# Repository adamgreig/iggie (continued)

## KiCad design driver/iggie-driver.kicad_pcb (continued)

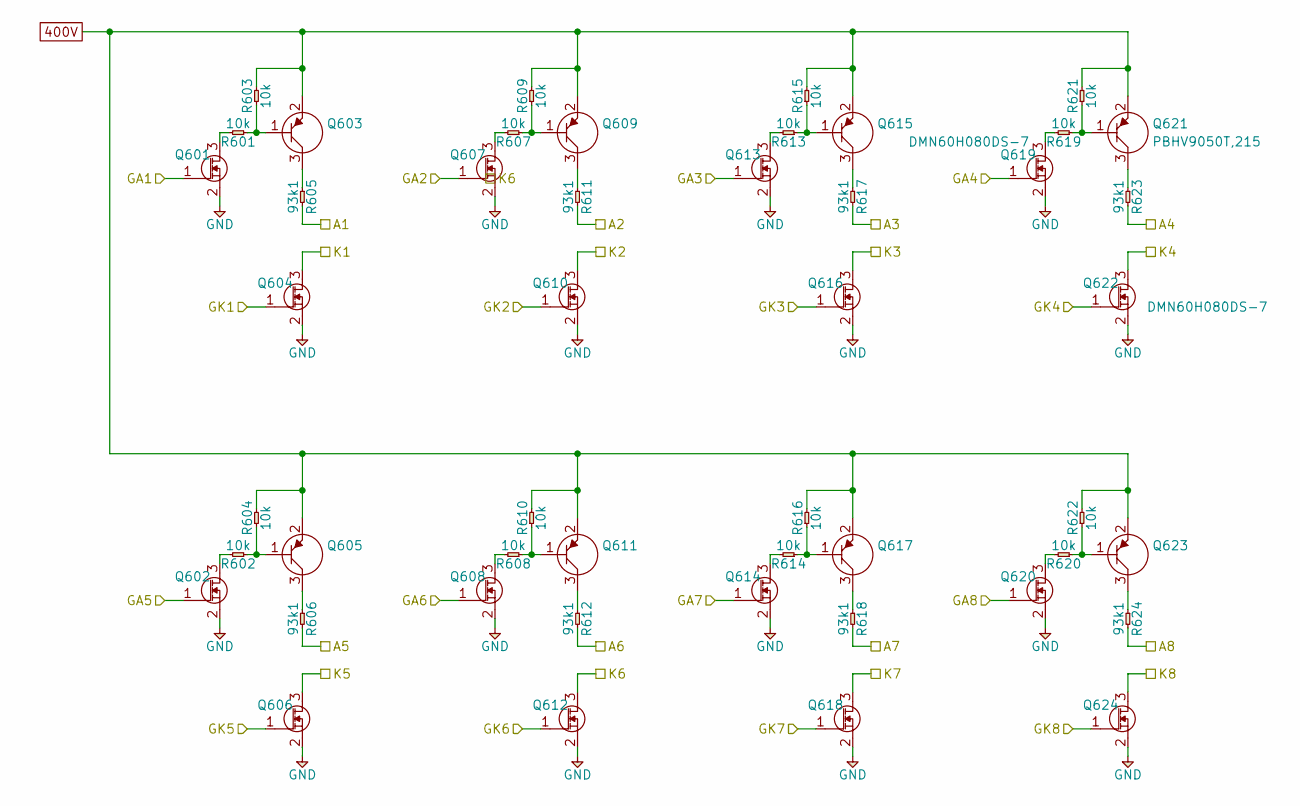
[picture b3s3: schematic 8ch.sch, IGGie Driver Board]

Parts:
Q301, Q302, Q304, Q306, Q307, Q308, Q310, Q312, Q313, Q314, Q316, Q318, Q319, Q320, Q322, Q324: DMN60H080DS-7; SOT-23; Farnell 3127344
Q303, Q305, Q309, Q311, Q315, Q317, Q321, Q323: PBHV9050T,215; SOT-23; Farnell 1829318
R301, R302, R303, R304, R307, R308, R309, R310, R313, R314, R315, R316, R319, R320, R321, R322: 10k; 1206; Voltage 500V; Farnell 1750850
R305, R306, R311, R312, R317, R318, R323, R324: 93k1; 1206; Voltage 500V; Farnell 2327389

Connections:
400V: Q303.2 (E), Q305.2 (E), Q309.2 (E), Q311.2 (E), Q315.2 (E), Q317.2 (E), Q321.2 (E), Q323.2 (E), R303.2, R304.2, R309.2, R310.2, R315.2, R316.2, R321.2, R322.2; also elsewhere on the board
/Channels/A1: R305.2; also elsewhere on the board
/Channels/A2: R311.2; also elsewhere on the board
/Channels/A3: R317.2; also elsewhere on the board
/Channels/A4: R323.2; also elsewhere on the board
/Channels/A5: R306.2; also elsewhere on the board
/Channels/A6: R312.2; also elsewhere on the board
/Channels/A7: R318.2; also elsewhere on the board
/Channels/A8: R324.2; also elsewhere on the board
/Channels/GA1: Q301.1 (G); also elsewhere on the board
/Channels/GA2: Q307.1 (G); also elsewhere on the board
/Channels/GA3: Q313.1 (G); also elsewhere on the board
/Channels/GA4: Q319.1 (G); also elsewhere on the board
/Channels/GA5: Q302.1 (G); also elsewhere on the board
/Channels/GA6: Q308.1 (G); also elsewhere on the board
/Channels/GA7: Q314.1 (G); also elsewhere on the board
/Channels/GA8: Q320.1 (G); also elsewhere on the board
/Channels/GK1: Q304.1 (G); also elsewhere on the board
/Channels/GK2: Q310.1 (G); also elsewhere on the board
/Channels/GK3: Q316.1 (G); also elsewhere on the board
/Channels/GK4: Q322.1 (G); also elsewhere on the board
/Channels/GK5: Q306.1 (G); also elsewhere on the board
/Channels/GK6: Q312.1 (G); also elsewhere on the board
/Channels/GK7: Q318.1 (G); also elsewhere on the board
/Channels/GK8: Q324.1 (G); also elsewhere on the board
/Channels/K1: Q304.3 (D); also elsewhere on the board
/Channels/K2: Q310.3 (D); also elsewhere on the board
/Channels/K3: Q316.3 (D); also elsewhere on the board
/Channels/K4: Q322.3 (D); also elsewhere on the board
/Channels/K5: Q306.3 (D); also elsewhere on the board
/Channels/K6: Q312.3 (D); also elsewhere on the board
/Channels/K7: Q318.3 (D); also elsewhere on the board
/Channels/K8: Q324.3 (D); also elsewhere on the board
GND: Q301.2 (S), Q302.2 (S), Q304.2 (S), Q306.2 (S), Q307.2 (S), Q308.2 (S), Q310.2 (S), Q312.2 (S), Q313.2 (S), Q314.2 (S), Q316.2 (S), Q318.2 (S), Q319.2 (S), Q320.2 (S), Q322.2 (S), Q324.2 (S); also elsewhere on the board
unnamed: Q301.3 (D), R301.2
unnamed: Q302.3 (D), R302.2
unnamed: Q303.1 (B), R301.1, R303.1
unnamed: Q303.3 (C), R305.1
unnamed: Q305.1 (B), R302.1, R304.1
unnamed: Q305.3 (C), R306.1
unnamed: Q307.3 (D), R307.2
unnamed: Q308.3 (D), R308.2
unnamed: Q309.1 (B), R307.1, R309.1
unnamed: Q309.3 (C), R311.1
unnamed: Q311.1 (B), R308.1, R310.1
unnamed: Q311.3 (C), R312.1
unnamed: Q313.3 (D), R313.2
unnamed: Q314.3 (D), R314.2
unnamed: Q315.1 (B), R313.1, R315.1
unnamed: Q315.3 (C), R317.1
unnamed: Q317.1 (B), R314.1, R316.1
unnamed: Q317.3 (C), R318.1
unnamed: Q319.3 (D), R319.2
unnamed: Q320.3 (D), R320.2
unnamed: Q321.1 (B), R319.1, R321.1
unnamed: Q321.3 (C), R323.1
unnamed: Q323.1 (B), R320.1, R322.1
unnamed: Q323.3 (C), R324.1

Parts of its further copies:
Q401, Q402, Q404, Q406, Q407, Q408, Q410, Q412, Q413, Q414, Q416, Q418, Q419, Q420, Q422, Q424, Q501, Q502, Q504, Q506, Q507, Q508, Q510, Q512, Q513, Q514, Q516, Q518, Q519, Q520, Q522, Q524, Q601, Q602, Q604, Q606, Q607, Q608, Q610, Q612, Q613, Q614, Q616, Q618, Q619, Q620, Q622, Q624: DMN60H080DS-7; SOT-23; Farnell 3127344
Q403, Q405, Q409, Q411, Q415, Q417, Q421, Q423, Q503, Q505, Q509, Q511, Q515, Q517, Q521, Q523, Q603, Q605, Q609, Q611, Q615, Q617, Q621, Q623: PBHV9050T,215; SOT-23; Farnell 1829318
R401, R402, R403, R404, R407, R408, R409, R410, R413, R414, R415, R416, R419, R420, R421, R422, R501, R502, R503, R504, R507, R508, R509, R510, R513, R514, R515, R516, R519, R520, R521, R522, R601, R602, R603, R604, R607, R608, R609, R610, R613, R614, R615, R616, R619, R620, R621, R622: 10k; 1206; Voltage 500V; Farnell 1750850
R405, R406, R411, R412, R417, R418, R423, R424, R505, R506, R511, R512, R517, R518, R523, R524, R605, R606, R611, R612, R617, R618, R623, R624: 93k1; 1206; Voltage 500V; Farnell 2327389

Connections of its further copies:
400V: Q403.2 (E), Q405.2 (E), Q409.2 (E), Q411.2 (E), Q415.2 (E), Q417.2 (E), Q421.2 (E), Q423.2 (E), Q503.2 (E), Q505.2 (E), Q509.2 (E), Q511.2 (E), Q515.2 (E), Q517.2 (E), Q521.2 (E), Q523.2 (E), Q603.2 (E), Q605.2 (E), Q609.2 (E), Q611.2 (E), Q615.2 (E), Q617.2 (E), Q621.2 (E), Q623.2 (E), R403.2, R404.2, R409.2, R410.2, R415.2, R416.2, R421.2, R422.2, R503.2, R504.2, R509.2, R510.2, R515.2, R516.2, R521.2, R522.2, R603.2, R604.2, R609.2, R610.2, R615.2, R616.2, R621.2, R622.2; also elsewhere on the board
/Channels/A9: R405.2; also elsewhere on the board
/Channels/A10: R411.2; also elsewhere on the board
/Channels/A11: R417.2; also elsewhere on the board
/Channels/A12: R423.2; also elsewhere on the board
/Channels/A13: R406.2; also elsewhere on the board
/Channels/A14: R412.2; also elsewhere on the board
/Channels/A15: R418.2; also elsewhere on the board
/Channels/A16: R424.2; also elsewhere on the board
/Channels/A17: R505.2; also elsewhere on the board
/Channels/A18: R511.2; also elsewhere on the board
/Channels/A19: R517.2; also elsewhere on the board
/Channels/A20: R523.2; also elsewhere on the board
/Channels/A21: R506.2; also elsewhere on the board
/Channels/A22: R512.2; also elsewhere on the board
/Channels/A23: R518.2; also elsewhere on the board
/Channels/A24: R524.2; also elsewhere on the board
/Channels/A25: R605.2; also elsewhere on the board
/Channels/A26: R611.2; also elsewhere on the board
/Channels/A27: R617.2; also elsewhere on the board
/Channels/A28: R623.2; also elsewhere on the board
/Channels/A29: R606.2; also elsewhere on the board
/Channels/A30: R612.2; also elsewhere on the board
/Channels/A31: R618.2; also elsewhere on the board
/Channels/A32: R624.2; also elsewhere on the board
/Channels/GA9: Q401.1 (G); also elsewhere on the board
/Channels/GA10: Q407.1 (G); also elsewhere on the board
/Channels/GA11: Q413.1 (G); also elsewhere on the board
/Channels/GA12: Q419.1 (G); also elsewhere on the board
/Channels/GA13: Q402.1 (G); also elsewhere on the board
/Channels/GA14: Q408.1 (G); also elsewhere on the board
/Channels/GA15: Q414.1 (G); also elsewhere on the board
/Channels/GA16: Q420.1 (G); also elsewhere on the board
/Channels/GA17: Q501.1 (G); also elsewhere on the board
/Channels/GA18: Q507.1 (G); also elsewhere on the board
/Channels/GA19: Q513.1 (G); also elsewhere on the board
/Channels/GA20: Q519.1 (G); also elsewhere on the board
/Channels/GA21: Q502.1 (G); also elsewhere on the board
/Channels/GA22: Q508.1 (G); also elsewhere on the board
/Channels/GA23: Q514.1 (G); also elsewhere on the board
/Channels/GA24: Q520.1 (G); also elsewhere on the board
/Channels/GA25: Q601.1 (G); also elsewhere on the board
/Channels/GA26: Q607.1 (G); also elsewhere on the board
/Channels/GA27: Q613.1 (G); also elsewhere on the board
/Channels/GA28: Q619.1 (G); also elsewhere on the board
/Channels/GA29: Q602.1 (G); also elsewhere on the board
/Channels/GA30: Q608.1 (G); also elsewhere on the board
/Channels/GA31: Q614.1 (G); also elsewhere on the board
/Channels/GA32: Q620.1 (G); also elsewhere on the board
/Channels/GK9: Q404.1 (G); also elsewhere on the board
/Channels/GK10: Q410.1 (G); also elsewhere on the board
/Channels/GK11: Q416.1 (G); also elsewhere on the board
/Channels/GK12: Q422.1 (G); also elsewhere on the board
/Channels/GK13: Q406.1 (G); also elsewhere on the board
/Channels/GK14: Q412.1 (G); also elsewhere on the board
/Channels/GK15: Q418.1 (G); also elsewhere on the board
/Channels/GK16: Q424.1 (G); also elsewhere on the board
/Channels/GK17: Q504.1 (G); also elsewhere on the board
/Channels/GK18: Q510.1 (G); also elsewhere on the board
/Channels/GK19: Q516.1 (G); also elsewhere on the board
/Channels/GK20: Q522.1 (G); also elsewhere on the board
/Channels/GK21: Q506.1 (G); also elsewhere on the board
/Channels/GK22: Q512.1 (G); also elsewhere on the board
/Channels/GK23: Q518.1 (G); also elsewhere on the board
/Channels/GK24: Q524.1 (G); also elsewhere on the board
/Channels/GK25: Q604.1 (G); also elsewhere on the board
/Channels/GK26: Q610.1 (G); also elsewhere on the board
/Channels/GK27: Q616.1 (G); also elsewhere on the board
/Channels/GK28: Q622.1 (G); also elsewhere on the board
/Channels/GK29: Q606.1 (G); also elsewhere on the board
/Channels/GK30: Q612.1 (G); also elsewhere on the board
/Channels/GK31: Q618.1 (G); also elsewhere on the board
/Channels/GK32: Q624.1 (G); also elsewhere on the board
/Channels/K9: Q404.3 (D); also elsewhere on the board
/Channels/K10: Q410.3 (D); also elsewhere on the board
/Channels/K11: Q416.3 (D); also elsewhere on the board
/Channels/K12: Q422.3 (D); also elsewhere on the board
/Channels/K13: Q406.3 (D); also elsewhere on the board
/Channels/K14: Q412.3 (D); also elsewhere on the board
/Channels/K15: Q418.3 (D); also elsewhere on the board
/Channels/K16: Q424.3 (D); also elsewhere on the board
/Channels/K17: Q504.3 (D); also elsewhere on the board
/Channels/K18: Q510.3 (D); also elsewhere on the board
/Channels/K19: Q516.3 (D); also elsewhere on the board
/Channels/K20: Q522.3 (D); also elsewhere on the board
/Channels/K21: Q506.3 (D); also elsewhere on the board
/Channels/K22: Q512.3 (D); also elsewhere on the board
/Channels/K23: Q518.3 (D); also elsewhere on the board
/Channels/K24: Q524.3 (D); also elsewhere on the board
/Channels/K25: Q604.3 (D); also elsewhere on the board
/Channels/K26: Q610.3 (D); also elsewhere on the board
/Channels/K27: Q616.3 (D); also elsewhere on the board
/Channels/K28: Q622.3 (D); also elsewhere on the board
/Channels/K29: Q606.3 (D); also elsewhere on the board
/Channels/K30: Q612.3 (D); also elsewhere on the board
/Channels/K31: Q618.3 (D); also elsewhere on the board
/Channels/K32: Q624.3 (D); also elsewhere on the board
GND: Q401.2 (S), Q402.2 (S), Q404.2 (S), Q406.2 (S), Q407.2 (S), Q408.2 (S), Q410.2 (S), Q412.2 (S), Q413.2 (S), Q414.2 (S), Q416.2 (S), Q418.2 (S), Q419.2 (S), Q420.2 (S), Q422.2 (S), Q424.2 (S), Q501.2 (S), Q502.2 (S), Q504.2 (S), Q506.2 (S), Q507.2 (S), Q508.2 (S), Q510.2 (S), Q512.2 (S), Q513.2 (S), Q514.2 (S), Q516.2 (S), Q518.2 (S), Q519.2 (S), Q520.2 (S), Q522.2 (S), Q524.2 (S), Q601.2 (S), Q602.2 (S), Q604.2 (S), Q606.2 (S), Q607.2 (S), Q608.2 (S), Q610.2 (S), Q612.2 (S), Q613.2 (S), Q614.2 (S), Q616.2 (S), Q618.2 (S), Q619.2 (S), Q620.2 (S), Q622.2 (S), Q624.2 (S); also elsewhere on the board
unnamed: Q401.3 (D), R401.2
unnamed: Q402.3 (D), R402.2
unnamed: Q403.1 (B), R401.1, R403.1
unnamed: Q403.3 (C), R405.1
unnamed: Q405.1 (B), R402.1, R404.1
unnamed: Q405.3 (C), R406.1
unnamed: Q407.3 (D), R407.2
unnamed: Q408.3 (D), R408.2
unnamed: Q409.1 (B), R407.1, R409.1
unnamed: Q409.3 (C), R411.1
unnamed: Q411.1 (B), R408.1, R410.1
unnamed: Q411.3 (C), R412.1
unnamed: Q413.3 (D), R413.2
unnamed: Q414.3 (D), R414.2
unnamed: Q415.1 (B), R413.1, R415.1
unnamed: Q415.3 (C), R417.1
unnamed: Q417.1 (B), R414.1, R416.1
unnamed: Q417.3 (C), R418.1
unnamed: Q419.3 (D), R419.2
unnamed: Q420.3 (D), R420.2
unnamed: Q421.1 (B), R419.1, R421.1
unnamed: Q421.3 (C), R423.1
unnamed: Q423.1 (B), R420.1, R422.1
unnamed: Q423.3 (C), R424.1
unnamed: Q501.3 (D), R501.2
unnamed: Q502.3 (D), R502.2
unnamed: Q503.1 (B), R501.1, R503.1
unnamed: Q503.3 (C), R505.1
unnamed: Q505.1 (B), R502.1, R504.1
unnamed: Q505.3 (C), R506.1
unnamed: Q507.3 (D), R507.2
unnamed: Q508.3 (D), R508.2
unnamed: Q509.1 (B), R507.1, R509.1
unnamed: Q509.3 (C), R511.1
unnamed: Q511.1 (B), R508.1, R510.1
unnamed: Q511.3 (C), R512.1
unnamed: Q513.3 (D), R513.2
unnamed: Q514.3 (D), R514.2
unnamed: Q515.1 (B), R513.1, R515.1
unnamed: Q515.3 (C), R517.1
unnamed: Q517.1 (B), R514.1, R516.1
unnamed: Q517.3 (C), R518.1
unnamed: Q519.3 (D), R519.2
unnamed: Q520.3 (D), R520.2
unnamed: Q521.1 (B), R519.1, R521.1
unnamed: Q521.3 (C), R523.1
unnamed: Q523.1 (B), R520.1, R522.1
unnamed: Q523.3 (C), R524.1
unnamed: Q601.3 (D), R601.2
unnamed: Q602.3 (D), R602.2
unnamed: Q603.1 (B), R601.1, R603.1
unnamed: Q603.3 (C), R605.1
unnamed: Q605.1 (B), R602.1, R604.1
unnamed: Q605.3 (C), R606.1
unnamed: Q607.3 (D), R607.2
unnamed: Q608.3 (D), R608.2
unnamed: Q609.1 (B), R607.1, R609.1
unnamed: Q609.3 (C), R611.1
unnamed: Q611.1 (B), R608.1, R610.1
unnamed: Q611.3 (C), R612.1
unnamed: Q613.3 (D), R613.2
unnamed: Q614.3 (D), R614.2
unnamed: Q615.1 (B), R613.1, R615.1
unnamed: Q615.3 (C), R617.1
unnamed: Q617.1 (B), R614.1, R616.1
unnamed: Q617.3 (C), R618.1
unnamed: Q619.3 (D), R619.2
unnamed: Q620.3 (D), R620.2
unnamed: Q621.1 (B), R619.1, R621.1
unnamed: Q621.3 (C), R623.1
unnamed: Q623.1 (B), R620.1, R622.1
unnamed: Q623.3 (C), R624.1

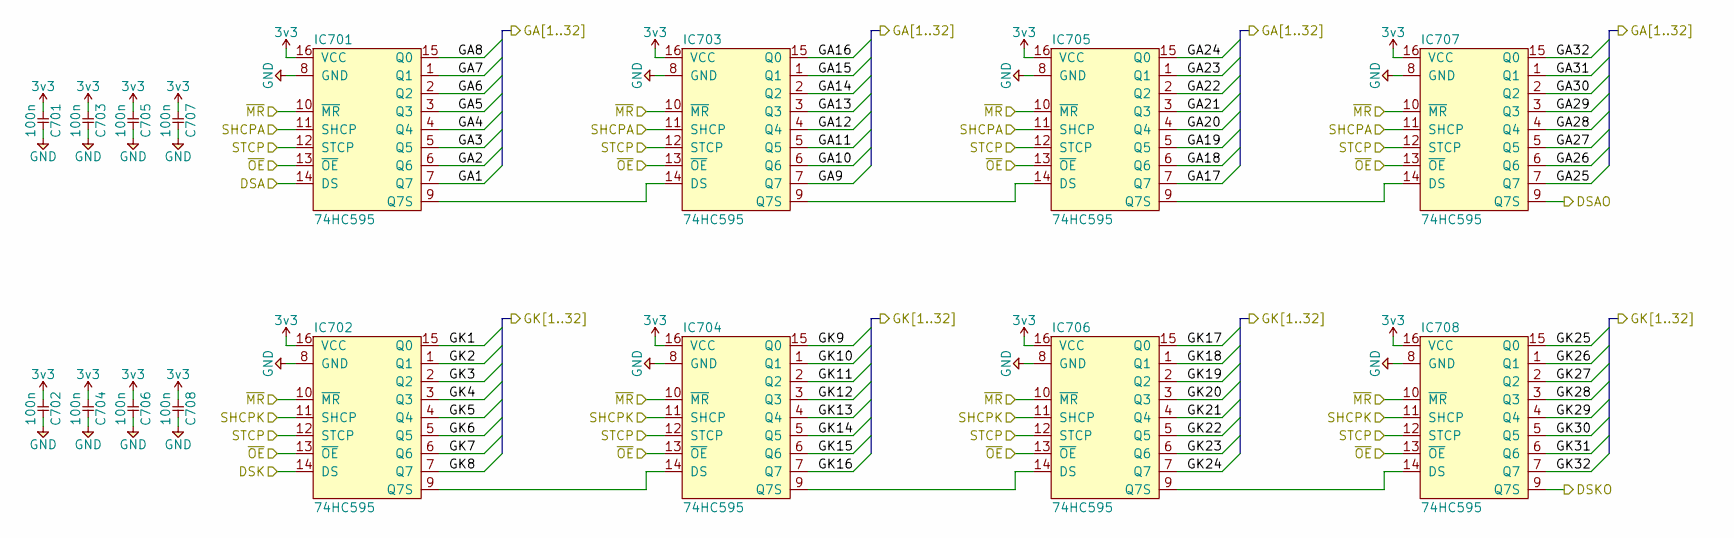
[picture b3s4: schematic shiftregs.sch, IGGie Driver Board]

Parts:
C701, C702, C703, C704, C705, C706, C707, C708: 100n; 0603; Voltage 50V; Farnell 2320803
IC701, IC702, IC703, IC704, IC705, IC706, IC707, IC708: 74HC595; TSSOP-16; Farnell 1607848

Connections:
3v3: C701.1, C702.1, C703.1, C704.1, C705.1, C706.1, C707.1, C708.1, IC701.16 (VCC), IC702.16 (VCC), IC703.16 (VCC), IC704.16 (VCC), IC705.16 (VCC), IC706.16 (VCC), IC707.16 (VCC), IC708.16 (VCC); also elsewhere on the board
/ACLK: IC701.11 (SHCP), IC703.11 (SHCP), IC705.11 (SHCP), IC707.11 (SHCP); also elsewhere on the board
/ADAT: IC701.14 (DS); also elsewhere on the board
/Channels/AOUT: IC707.9 (Q7S); also elsewhere on the board
/Channels/GA1: IC701.7 (Q7); also elsewhere on the board
/Channels/GA2: IC701.6 (Q6); also elsewhere on the board
/Channels/GA3: IC701.5 (Q5); also elsewhere on the board
/Channels/GA4: IC701.4 (Q4); also elsewhere on the board
/Channels/GA5: IC701.3 (Q3); also elsewhere on the board
/Channels/GA6: IC701.2 (Q2); also elsewhere on the board
/Channels/GA7: IC701.1 (Q1); also elsewhere on the board
/Channels/GA8: IC701.15 (Q0); also elsewhere on the board
/Channels/GA9: IC703.7 (Q7); also elsewhere on the board
/Channels/GA10: IC703.6 (Q6); also elsewhere on the board
/Channels/GA11: IC703.5 (Q5); also elsewhere on the board
/Channels/GA12: IC703.4 (Q4); also elsewhere on the board
/Channels/GA13: IC703.3 (Q3); also elsewhere on the board
/Channels/GA14: IC703.2 (Q2); also elsewhere on the board
/Channels/GA15: IC703.1 (Q1); also elsewhere on the board
/Channels/GA16: IC703.15 (Q0); also elsewhere on the board
/Channels/GA17: IC705.7 (Q7); also elsewhere on the board
/Channels/GA18: IC705.6 (Q6); also elsewhere on the board
/Channels/GA19: IC705.5 (Q5); also elsewhere on the board
/Channels/GA20: IC705.4 (Q4); also elsewhere on the board
/Channels/GA21: IC705.3 (Q3); also elsewhere on the board
/Channels/GA22: IC705.2 (Q2); also elsewhere on the board
/Channels/GA23: IC705.1 (Q1); also elsewhere on the board
/Channels/GA24: IC705.15 (Q0); also elsewhere on the board
/Channels/GA25: IC707.7 (Q7); also elsewhere on the board
/Channels/GA26: IC707.6 (Q6); also elsewhere on the board
/Channels/GA27: IC707.5 (Q5); also elsewhere on the board
/Channels/GA28: IC707.4 (Q4); also elsewhere on the board
/Channels/GA29: IC707.3 (Q3); also elsewhere on the board
/Channels/GA30: IC707.2 (Q2); also elsewhere on the board
/Channels/GA31: IC707.1 (Q1); also elsewhere on the board
/Channels/GA32: IC707.15 (Q0); also elsewhere on the board
/Channels/GK1: IC702.15 (Q0); also elsewhere on the board
/Channels/GK2: IC702.1 (Q1); also elsewhere on the board
/Channels/GK3: IC702.2 (Q2); also elsewhere on the board
/Channels/GK4: IC702.3 (Q3); also elsewhere on the board
/Channels/GK5: IC702.4 (Q4); also elsewhere on the board
/Channels/GK6: IC702.5 (Q5); also elsewhere on the board
/Channels/GK7: IC702.6 (Q6); also elsewhere on the board
/Channels/GK8: IC702.7 (Q7); also elsewhere on the board
/Channels/GK9: IC704.15 (Q0); also elsewhere on the board
/Channels/GK10: IC704.1 (Q1); also elsewhere on the board
/Channels/GK11: IC704.2 (Q2); also elsewhere on the board
/Channels/GK12: IC704.3 (Q3); also elsewhere on the board
/Channels/GK13: IC704.4 (Q4); also elsewhere on the board
/Channels/GK14: IC704.5 (Q5); also elsewhere on the board
/Channels/GK15: IC704.6 (Q6); also elsewhere on the board
/Channels/GK16: IC704.7 (Q7); also elsewhere on the board
/Channels/GK17: IC706.15 (Q0); also elsewhere on the board
/Channels/GK18: IC706.1 (Q1); also elsewhere on the board
/Channels/GK19: IC706.2 (Q2); also elsewhere on the board
/Channels/GK20: IC706.3 (Q3); also elsewhere on the board
/Channels/GK21: IC706.4 (Q4); also elsewhere on the board
/Channels/GK22: IC706.5 (Q5); also elsewhere on the board
/Channels/GK23: IC706.6 (Q6); also elsewhere on the board
/Channels/GK24: IC706.7 (Q7); also elsewhere on the board
/Channels/GK25: IC708.15 (Q0); also elsewhere on the board
/Channels/GK26: IC708.1 (Q1); also elsewhere on the board
/Channels/GK27: IC708.2 (Q2); also elsewhere on the board
/Channels/GK28: IC708.3 (Q3); also elsewhere on the board
/Channels/GK29: IC708.4 (Q4); also elsewhere on the board
/Channels/GK30: IC708.5 (Q5); also elsewhere on the board
/Channels/GK31: IC708.6 (Q6); also elsewhere on the board
/Channels/GK32: IC708.7 (Q7); also elsewhere on the board
/Channels/KOUT: IC708.9 (Q7S); also elsewhere on the board
/KCLK: IC702.11 (SHCP), IC704.11 (SHCP), IC706.11 (SHCP), IC708.11 (SHCP); also elsewhere on the board
/KDAT: IC702.14 (DS); also elsewhere on the board
/STCP: IC701.12 (STCP), IC702.12 (STCP), IC703.12 (STCP), IC704.12 (STCP), IC705.12 (STCP), IC706.12 (STCP), IC707.12 (STCP), IC708.12 (STCP); also elsewhere on the board
/~MR: IC701.10 (~MR), IC702.10 (~MR), IC703.10 (~MR), IC704.10 (~MR), IC705.10 (~MR), IC706.10 (~MR), IC707.10 (~MR), IC708.10 (~MR); also elsewhere on the board
/~OE: IC701.13 (~OE), IC702.13 (~OE), IC703.13 (~OE), IC704.13 (~OE), IC705.13 (~OE), IC706.13 (~OE), IC707.13 (~OE), IC708.13 (~OE); also elsewhere on the board
GND: C701.2, C702.2, C703.2, C704.2, C705.2, C706.2, C707.2, C708.2, IC701.8 (GND), IC702.8 (GND), IC703.8 (GND), IC704.8 (GND), IC705.8 (GND), IC706.8 (GND), IC707.8 (GND), IC708.8 (GND); also elsewhere on the board
unnamed: IC701.9 (Q7S), IC703.14 (DS)
unnamed: IC702.9 (Q7S), IC704.14 (DS)
unnamed: IC703.9 (Q7S), IC705.14 (DS)
unnamed: IC704.9 (Q7S), IC706.14 (DS)
unnamed: IC705.9 (Q7S), IC707.14 (DS)
unnamed: IC706.9 (Q7S), IC708.14 (DS)

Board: 2 copper layers, 253 parts (0 on the bottom side), 274 nets, no tracks yet.

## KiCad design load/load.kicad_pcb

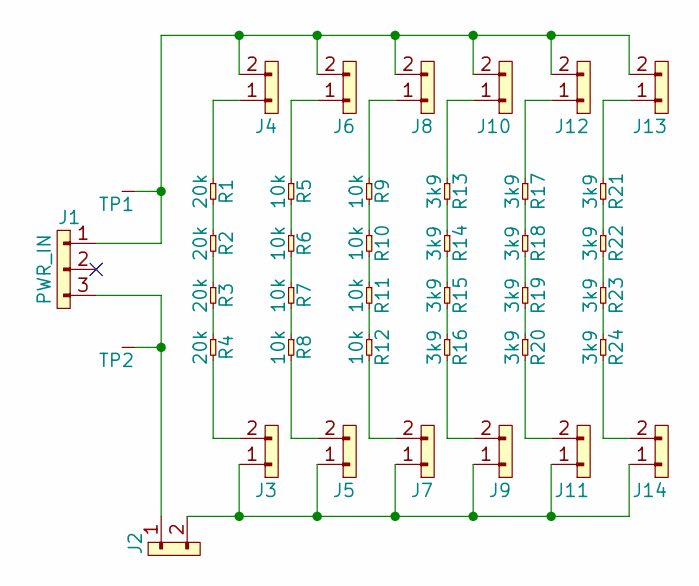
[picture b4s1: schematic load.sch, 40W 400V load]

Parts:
J1: PWR_IN; MOLEX-KK-254P-03
J2, J3, J4, J5, J6, J7, J8, J9, J10, J11, J12, J13, J14: CONN_01x02; SIL-254P-02
R1, R2, R3, R4: 20k; 2512; Farnell 2380982
R5, R6, R7, R8, R9, R10, R11, R12: 10k; 2512; Farnell 2861351
R13, R14, R15, R16, R17, R18, R19, R20, R21, R22, R23, R24: 3k9; 2512; Farnell 2476502
TP1, TP2: TESTPAD; KEYSTONE5016

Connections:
unnamed: J1.1, J4.2, J6.2, J8.2, J10.2, J12.2, J13.2, TP1.1
unnamed: J1.3, J2.1, TP2.1
unnamed: J3.2, R4.2
unnamed: J4.1, R1.1
unnamed: J5.2, R8.2
unnamed: J6.1, R5.1
unnamed: J7.2, R12.2
unnamed: J8.1, R9.1
unnamed: J9.2, R16.2
unnamed: J10.1, R13.1
unnamed: J2.2, J3.1, J5.1, J7.1, J9.1, J11.1, J14.1
unnamed: J11.2, R20.2
unnamed: J12.1, R17.1
unnamed: J13.1, R21.1
unnamed: J14.2, R24.2
unnamed: R1.2, R2.1
unnamed: R2.2, R3.1
unnamed: R3.2, R4.1
unnamed: R5.2, R6.1
unnamed: R6.2, R7.1
unnamed: R7.2, R8.1
unnamed: R9.2, R10.1
unnamed: R10.2, R11.1
unnamed: R11.2, R12.1
unnamed: R13.2, R14.1
unnamed: R14.2, R15.1
unnamed: R15.2, R16.1
unnamed: R17.2, R18.1
unnamed: R18.2, R19.1
unnamed: R19.2, R20.1
unnamed: R21.2, R22.1
unnamed: R22.2, R23.1
unnamed: R23.2, R24.1

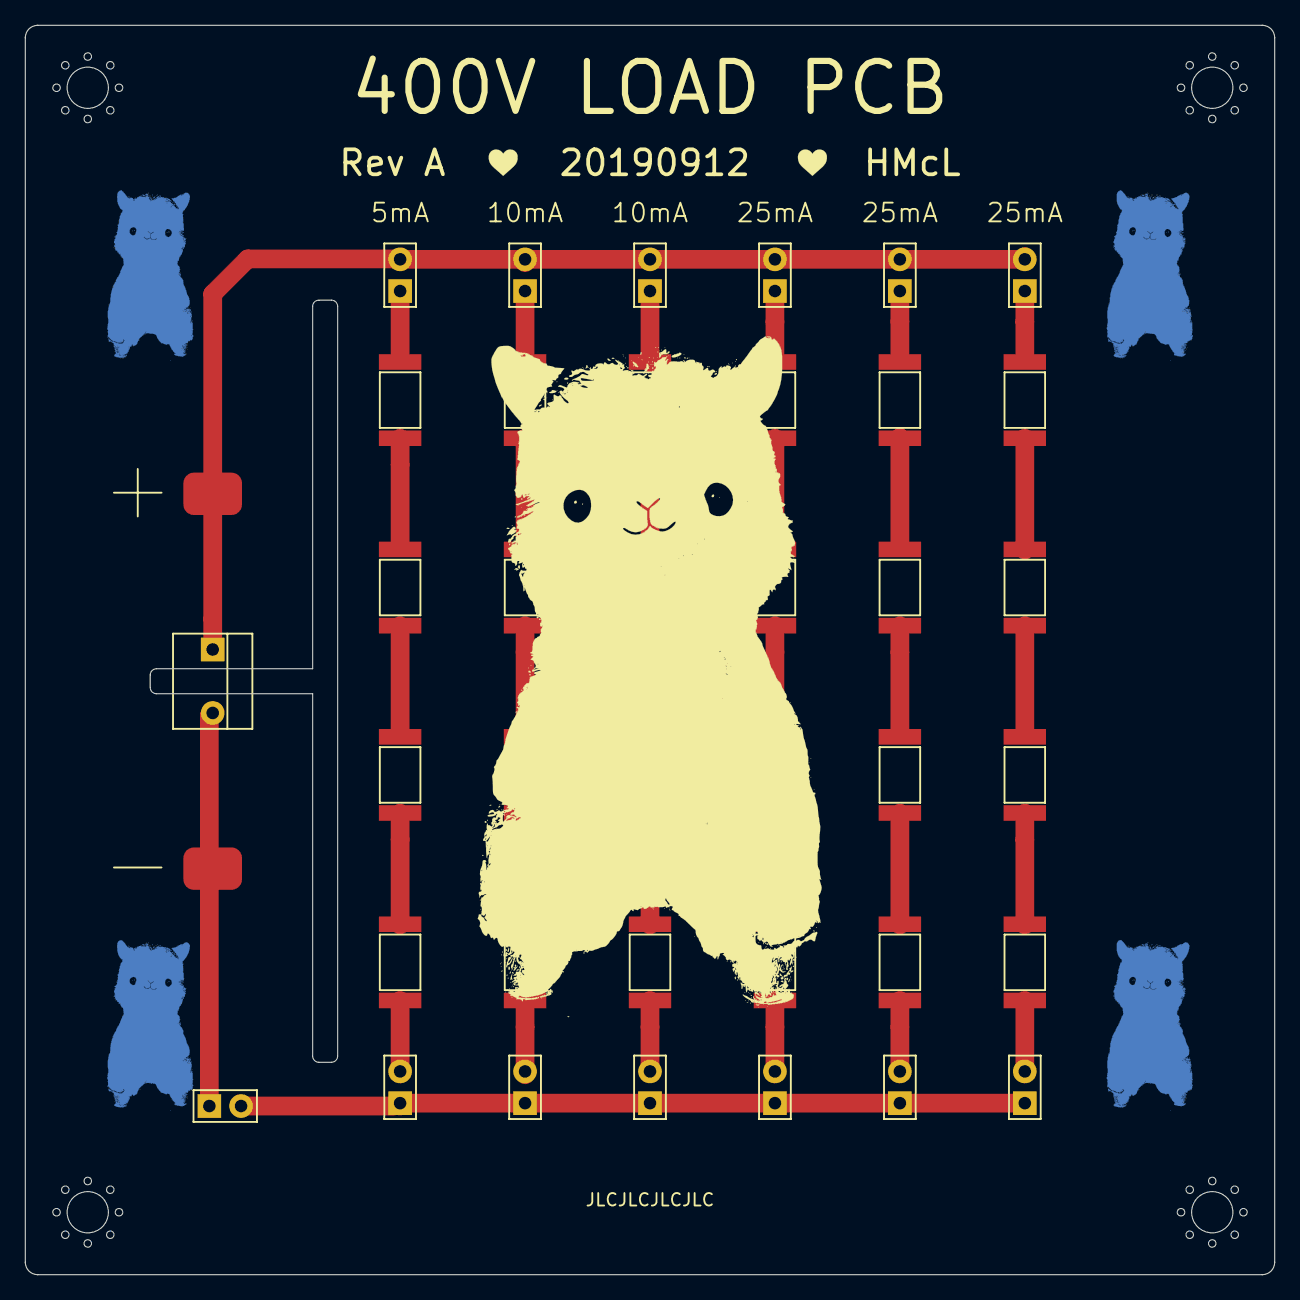
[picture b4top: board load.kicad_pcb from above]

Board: 2 copper layers, 100.0 x 100.0 mm, 40 parts (0 on the bottom side), 33 nets.

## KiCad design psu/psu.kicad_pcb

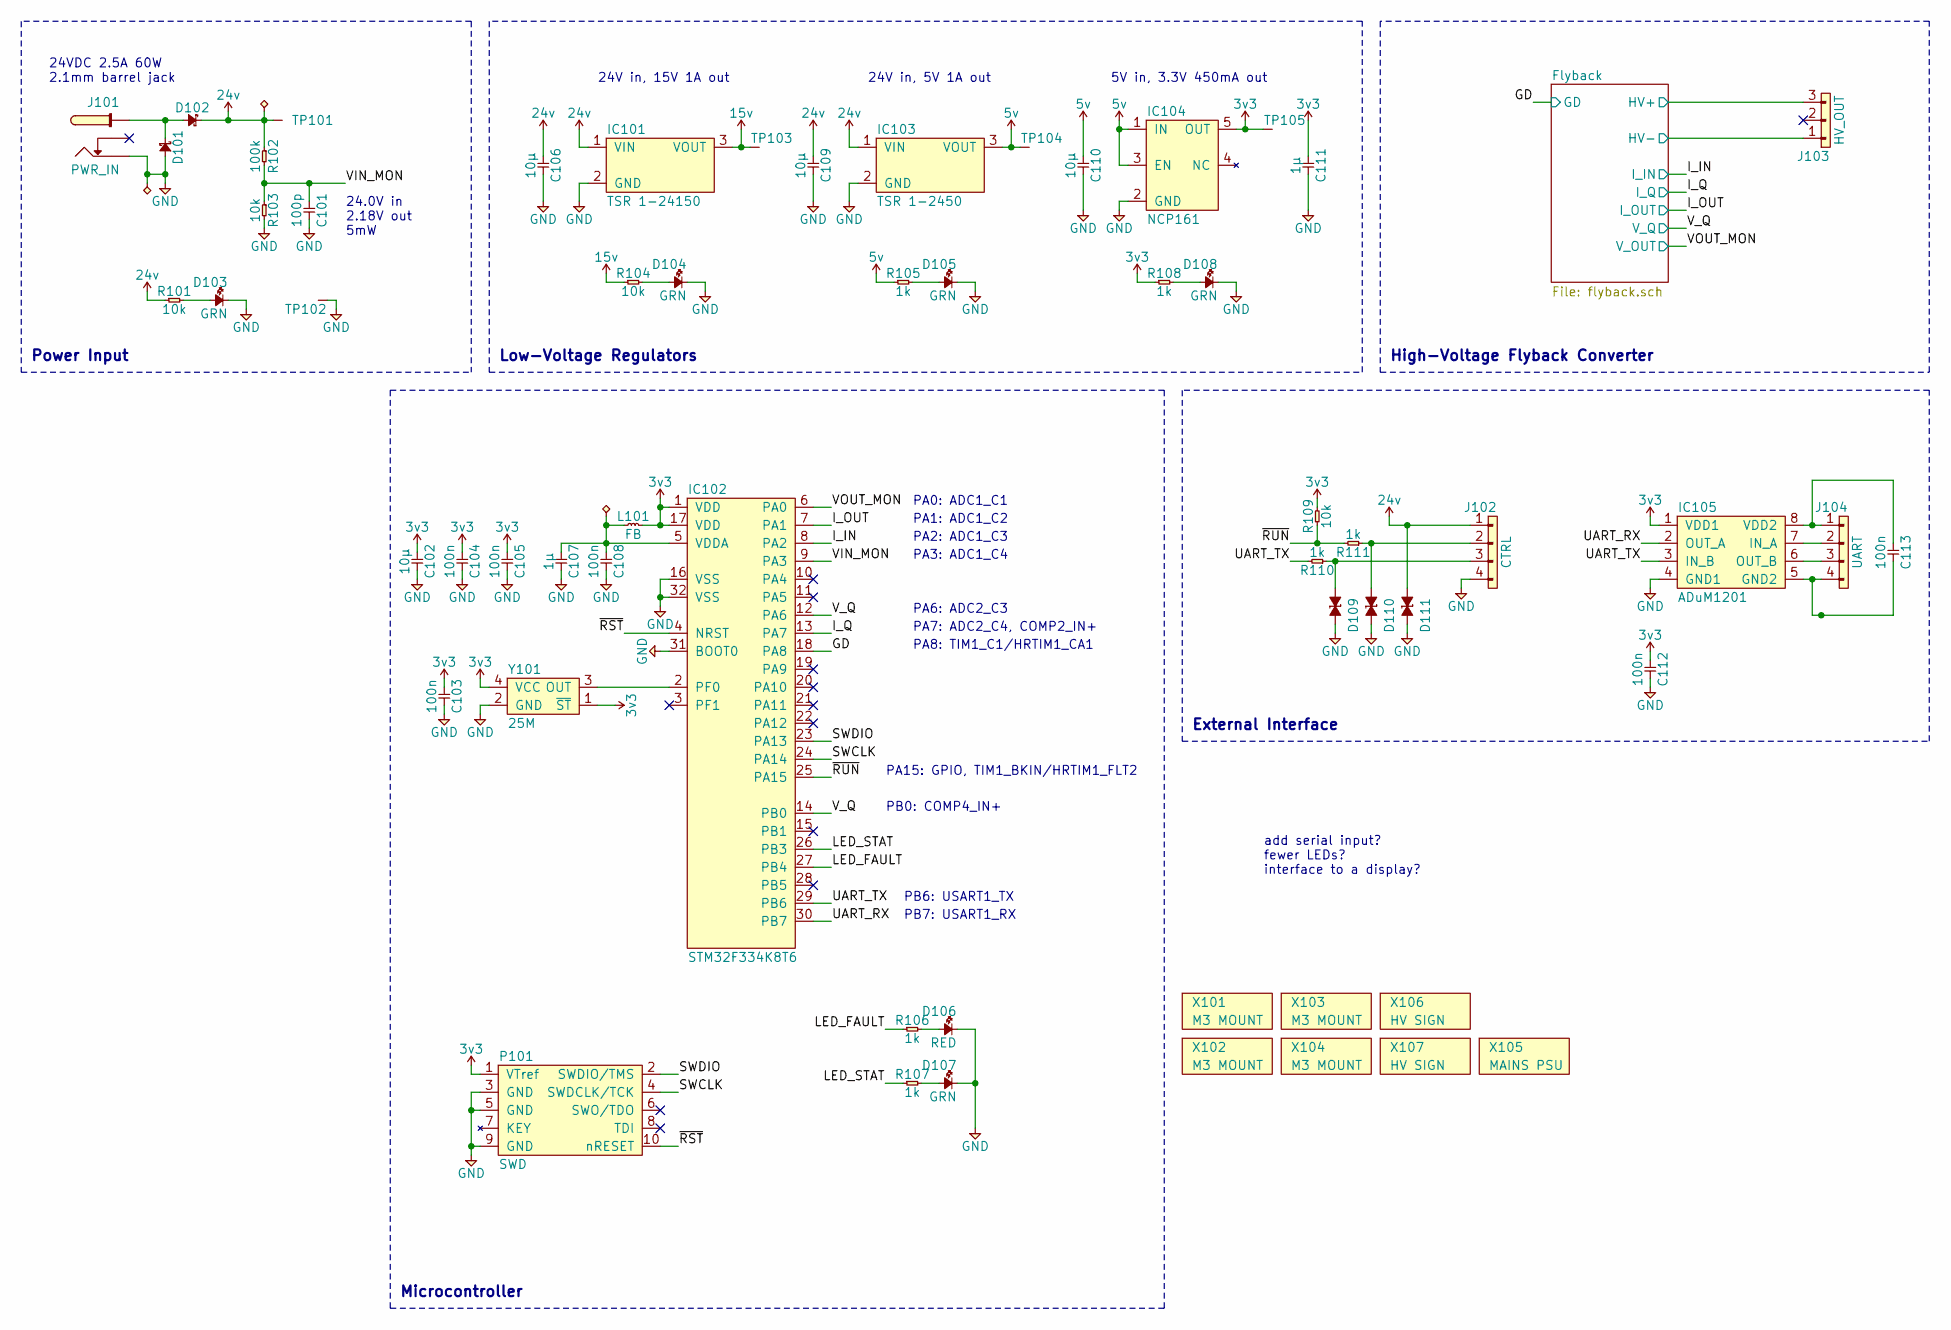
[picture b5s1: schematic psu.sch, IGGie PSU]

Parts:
C101: 100p; 0603; Voltage 50V; Farnell 9406115
C102, C106, C109, C110: 10µ; 1210; Voltage 50V; Farnell 2781426
C103, C104, C105, C108, C112, C113: 100n; 0603; Voltage 50V; Farnell 2320803
C107, C111: 1µ; 0603; Voltage 16V; Farnell 2320814
D101: SMAJ58A; DO-214AC-SMA; Farnell 1899460
D102: VSSC520S-M3/9AT; DO-214AB-SMC; Farnell 1859669
D103, D104, D105, D107, D108: GRN; 0603-LED; Farnell 2290328
D106: RED; 0603-LED; Farnell 2290329
D109, D110, D111: ESD_DIODE; 0603; Voltage 24V; Farnell 2368174
IC101: TSR 1-24150; TSR1; Farnell 1672131
IC102: STM32F334K8T6; LQFP-32; Farnell 2469571
IC103: TSR 1-2450; TSR1; Farnell 1696320
IC104: NCP161; SOT-23-5; Farnell 3131472
IC105: ADuM1201; SOIC-8; Farnell 1078200
J101: PWR_IN; BARRELJACK
J102: CTRL; MOLEX-KK-254P-04; Farnell 1360132
J103: HV_OUT; MOLEX-KK-254P-03; Farnell 1360131
J104: UART; MOLEX-PICOBLADE-53398-0471; Farnell 1125367
L101: FB; 0603; Farnell 1515747
P101: SWD; FTSH-105-01-L-DV-K; Farnell 2856437
R101, R103, R104, R109: 10k; 0603; Voltage 50V; Farnell 2447230
R102: 100k; 0603; Voltage 50V; Farnell 2447226
R105, R106, R107, R108, R110, R111: 1k; 0603; Voltage 50V; Farnell 2447272
TP101, TP103, TP104, TP105: TESTPAD
TP102: TESTPAD; KEYSTONE5016
X101, X102, X103, X104: M3 MOUNT; M3_MOUNT
X105: MAINS PSU; Farnell 2815916
X106, X107: HV SIGN; hv
Y101: 25M; XTAL-25x20; Farnell 2849479

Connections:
3v3: C102.1, C103.1, C104.1, C105.1, C111.1, C112.1, IC102.1 (VDD), IC102.17 (VDD), IC104.5 (OUT), IC105.1 (VDD1), L101.2, P101.1 (VTref), R108.1, R109.2, TP105.1, Y101.1 (~ST), Y101.4 (VCC); also elsewhere on the board
5v: C110.1, IC103.3 (VOUT), IC104.1 (IN), IC104.3 (EN), R105.1, TP104.1; also elsewhere on the board
15v: IC101.3 (VOUT), R104.1, TP103.1; also elsewhere on the board
24v: C106.1, C109.1, D102.1, D111.1, IC101.1 (VIN), IC103.1 (VIN), J102.1, R101.1, R102.1, TP101.1; also elsewhere on the board
/Flyback/HV+: J103.3; also elsewhere on the board
/GD: IC102.18 (PA8); also elsewhere on the board
/I_IN: IC102.8 (PA2); also elsewhere on the board
/I_OUT: IC102.7 (PA1); also elsewhere on the board
/I_Q: IC102.13 (PA7); also elsewhere on the board
/LED_FAULT: IC102.27 (PB4), R106.1
/LED_STAT: IC102.26 (PB3), R107.1
/SWCLK: IC102.24 (PA14), P101.4 (SWDCLK/TCK)
/SWDIO: IC102.23 (PA13), P101.2 (SWDIO/TMS)
/UART_RX: IC102.30 (PB7), IC105.2 (OUT_A)
/UART_TX: IC102.29 (PB6), IC105.3 (IN_B), R110.2
/VIN_MON: C101.1, IC102.9 (PA3), R102.2, R103.1
/VOUT_MON: IC102.6 (PA0); also elsewhere on the board
/V_Q: IC102.12 (PA6), IC102.14 (PB0); also elsewhere on the board
/~RST: IC102.4 (NRST), P101.10 (nRESET)
/~RUN: IC102.25 (PA15), R109.1, R111.2
GND: C101.2, C102.2, C103.2, C104.2, C105.2, C106.2, C107.2, C108.2, C109.2, C110.2, C111.2, C112.2, D101.2, D103.1, D104.1, D105.1, D106.1, D107.1, D108.1, D109.2, D110.2, D111.2, IC101.2 (GND), IC102.16 (VSS), IC102.31 (BOOT0), IC102.32 (VSS), IC103.2 (GND), IC104.2 (GND), IC105.4 (GND1), J101.3 (RING), J102.4, J103.1, P101.3 (GND), P101.5 (GND), P101.9 (GND), R103.2, TP102.1, Y101.2 (GND); also elsewhere on the board
unnamed: C107.1, C108.1, IC102.5 (VDDA), L101.1
unnamed: C113.1, IC105.8 (VDD2), J104.1
unnamed: C113.2, IC105.5 (GND2), J104.4
unnamed: D101.1, D102.2, J101.1 (TIP)
unnamed: D103.2, R101.2
unnamed: D104.2, R104.2
unnamed: D105.2, R105.2
unnamed: D106.2, R106.2
unnamed: D107.2, R107.2
unnamed: D108.2, R108.2
unnamed: D109.1, J102.3, R110.1
unnamed: D110.1, J102.2, R111.1
unnamed: IC102.2 (PF0), Y101.3 (OUT)
unnamed: IC105.6 (OUT_B), J104.3
unnamed: IC105.7 (IN_A), J104.2

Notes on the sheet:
24VDC 2.5A 60W 2.1mm barrel jack
24V in, 5V 1A out
5V in, 3.3V 450mA out
PB6: USART1_TX
Power Input
External Interface
Microcontroller
PA0: ADC1_C1
PA1: ADC1_C2
PA2: ADC1_C3
24V in, 15V 1A out
PA3: ADC1_C4
24.0V in 2.18V out 5mW
Low-Voltage Regulators
High-Voltage Flyback Converter
PA15: GPIO, TIM1_BKIN/HRTIM1_FLT2
PA8: TIM1_C1/HRTIM1_CA1
PA7: ADC2_C4, COMP2_IN+
add serial input? fewer LEDs? interface to a display?
PB0: COMP4_IN+
PA6: ADC2_C3
PB7: USART1_RX
